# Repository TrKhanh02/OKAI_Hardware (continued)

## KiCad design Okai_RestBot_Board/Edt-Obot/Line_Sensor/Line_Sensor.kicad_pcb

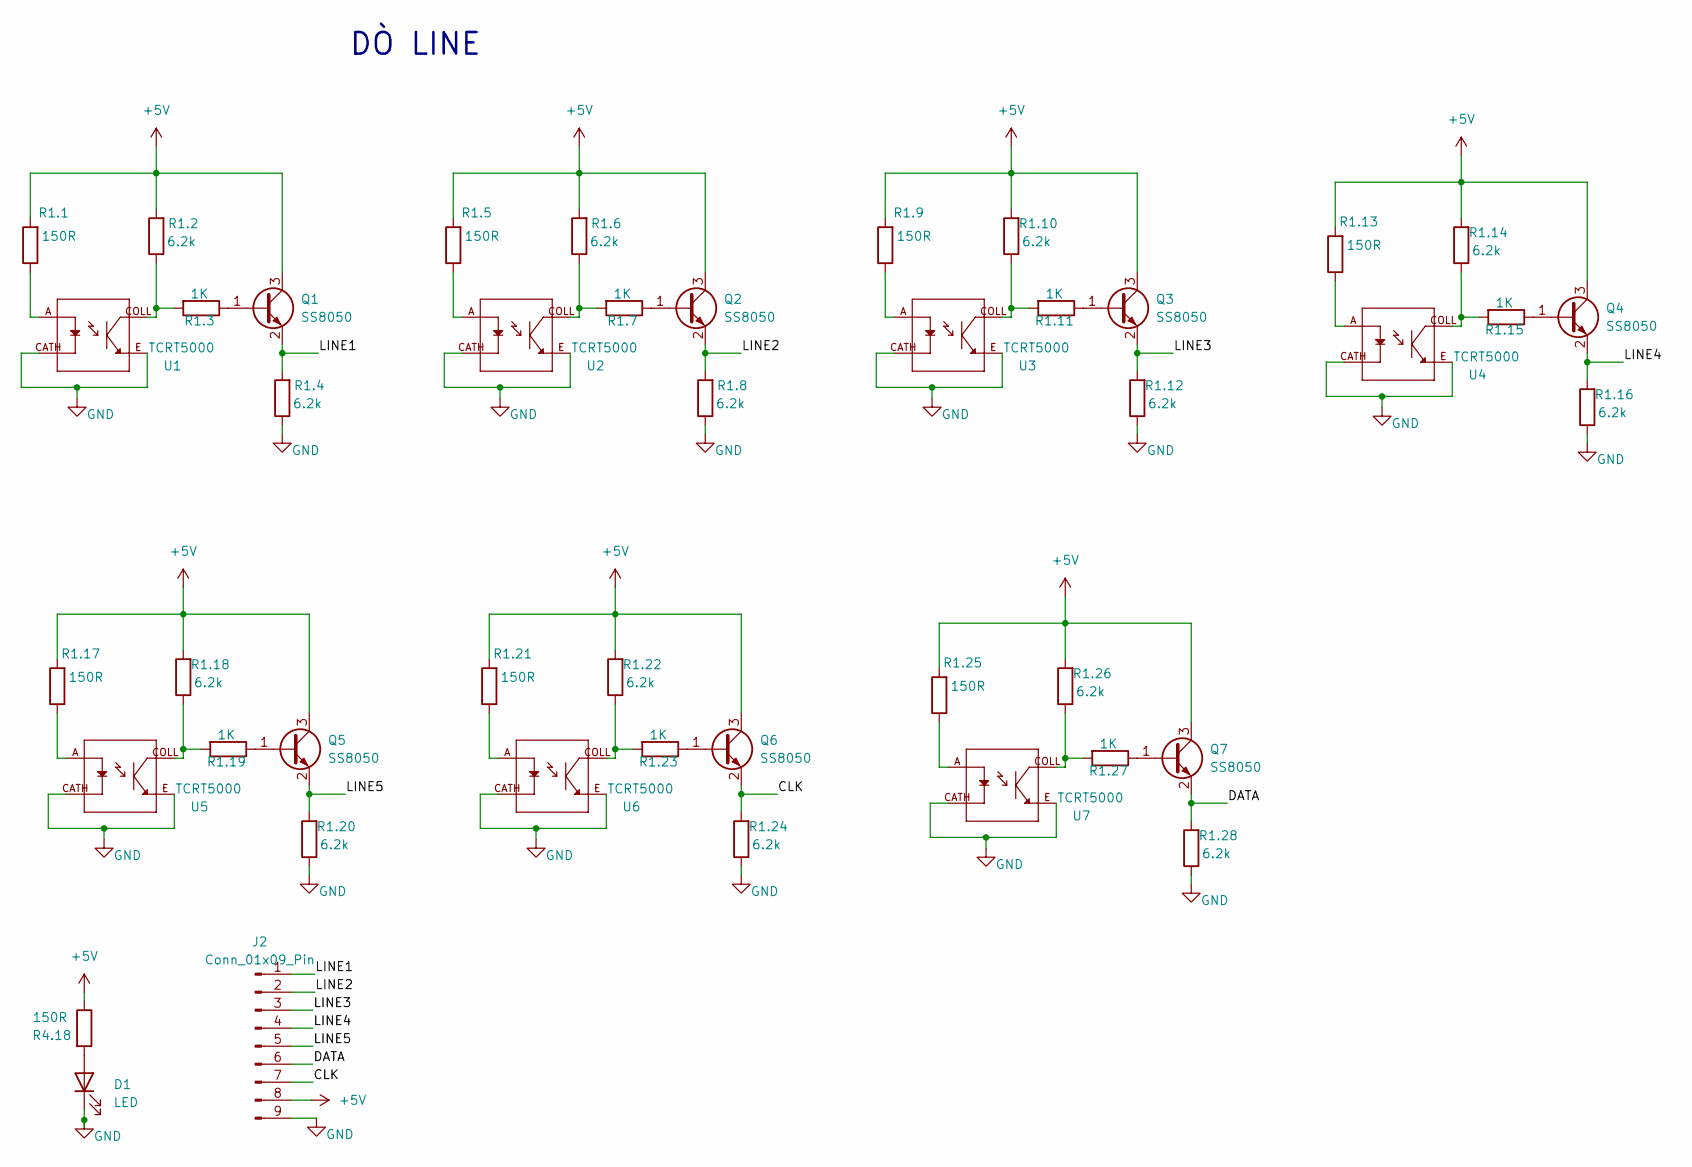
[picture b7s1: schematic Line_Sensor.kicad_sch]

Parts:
D1: LED; LED_0805_2012Metric
J2: Conn_01x09_Pin; PinHeader_1x09_P2.54mm_Vertical
Q1, Q2, Q3, Q4, Q5, Q6, Q7: SS8050; SOT-23
R1.1, R1.5, R1.9, R1.13, R1.17, R1.21, R1.25, R4.18: 150R; R_0805_2012Metric
R1.2, R1.4, R1.6, R1.8, R1.10, R1.12, R1.14, R1.16, R1.18, R1.20, R1.22, R1.24, R1.26, R1.28: 6.2k; R_0805_2012Metric
R1.3, R1.7, R1.11, R1.15, R1.19, R1.23, R1.27: 1K; R_0805_2012Metric
U1, U2, U3, U4, U5, U6, U7: TCRT5000; OPTO_TCRT5000; PARTREV 1.7

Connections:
+5V: J2.8, Q1.3 (C), Q2.3 (C), Q3.3 (C), Q4.3 (C), Q5.3 (C), Q6.3 (C), Q7.3 (C), R1.1.2, R1.2.2, R1.5.2, R1.6.2, R1.9.2, R1.10.2, R1.13.2, R1.14.2, R1.17.2, R1.18.2, R1.21.2, R1.22.2, R1.25.2, R1.26.2, R4.18.1
/CLK: J2.7, Q6.2 (E), R1.24.2
/DATA: J2.6, Q7.2 (E), R1.28.2
/LINE1: J2.1, Q1.2 (E), R1.4.2
/LINE2: J2.2, Q2.2 (E), R1.8.2
/LINE3: J2.3, Q3.2 (E), R1.12.2
/LINE4: J2.4, Q4.2 (E), R1.16.2
/LINE5: J2.5, Q5.2 (E), R1.20.2
GND: D1.1 (K), J2.9, R1.4.1, R1.8.1, R1.12.1, R1.16.1, R1.20.1, R1.24.1, R1.28.1, U1.CATH, U1.E, U2.CATH, U2.E, U3.CATH, U3.E, U4.CATH, U4.E, U5.CATH, U5.E, U6.CATH, U6.E, U7.CATH, U7.E
unnamed: D1.2 (A), R4.18.2
unnamed: Q1.1 (B), R1.3.1
unnamed: Q2.1 (B), R1.7.1
unnamed: Q3.1 (B), R1.11.1
unnamed: Q4.1 (B), R1.15.1
unnamed: Q5.1 (B), R1.19.1
unnamed: Q6.1 (B), R1.23.1
unnamed: Q7.1 (B), R1.27.1
unnamed: R1.1.1, U1.A
unnamed: R1.2.1, R1.3.2, U1.COLL
unnamed: R1.5.1, U2.A
unnamed: R1.6.1, R1.7.2, U2.COLL
unnamed: R1.9.1, U3.A
unnamed: R1.10.1, R1.11.2, U3.COLL
unnamed: R1.13.1, U4.A
unnamed: R1.14.1, R1.15.2, U4.COLL
unnamed: R1.17.1, U5.A
unnamed: R1.18.1, R1.19.2, U5.COLL
unnamed: R1.21.1, U6.A
unnamed: R1.22.1, R1.23.2, U6.COLL
unnamed: R1.25.1, U7.A
unnamed: R1.26.1, R1.27.2, U7.COLL

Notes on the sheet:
DÒ LINE

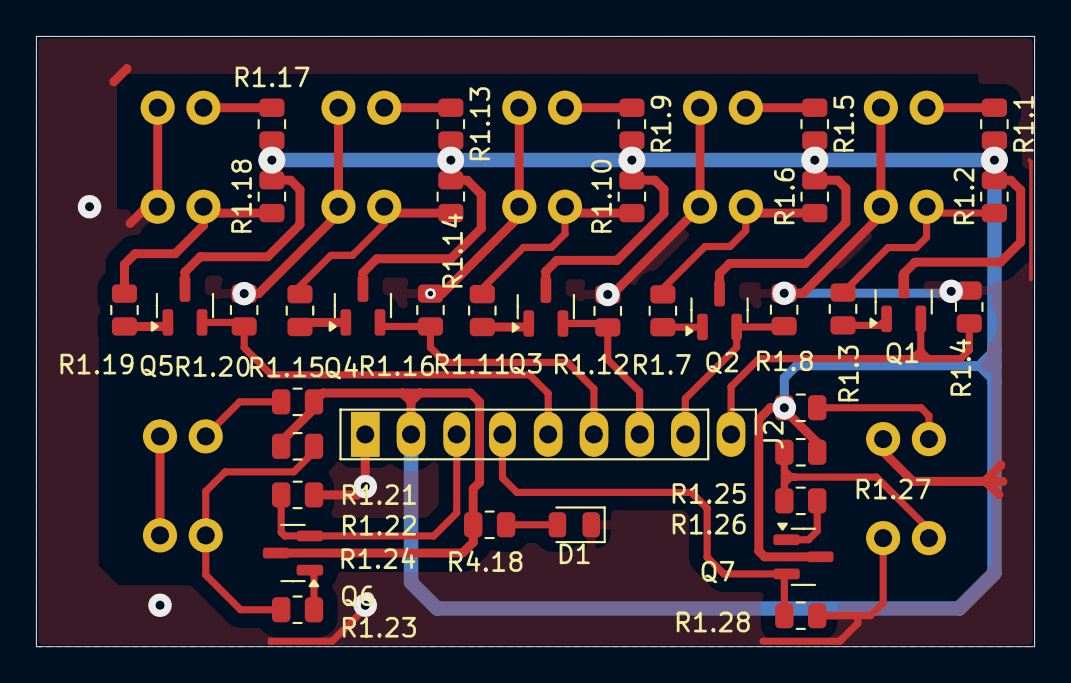
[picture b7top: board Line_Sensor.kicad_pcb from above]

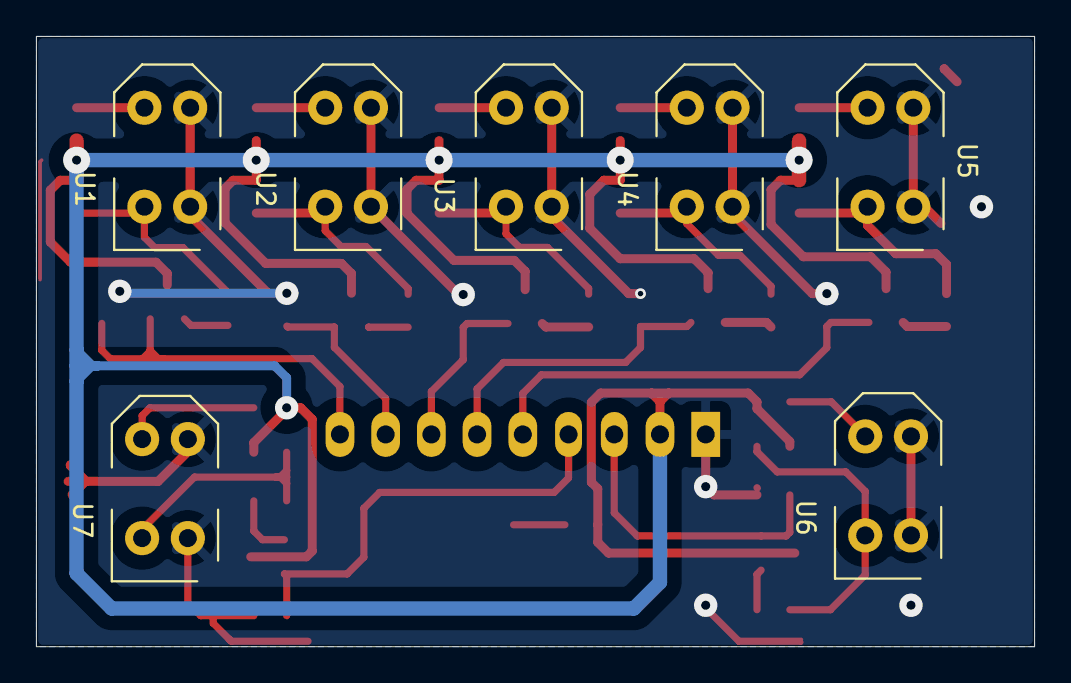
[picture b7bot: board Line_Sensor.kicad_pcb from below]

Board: 2 copper layers, 55.4 x 33.9 mm, 45 parts (7 on the bottom side), 31 nets.

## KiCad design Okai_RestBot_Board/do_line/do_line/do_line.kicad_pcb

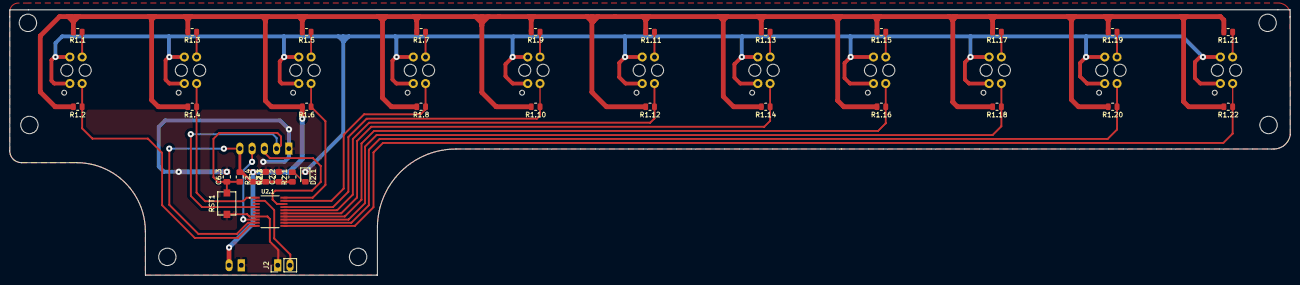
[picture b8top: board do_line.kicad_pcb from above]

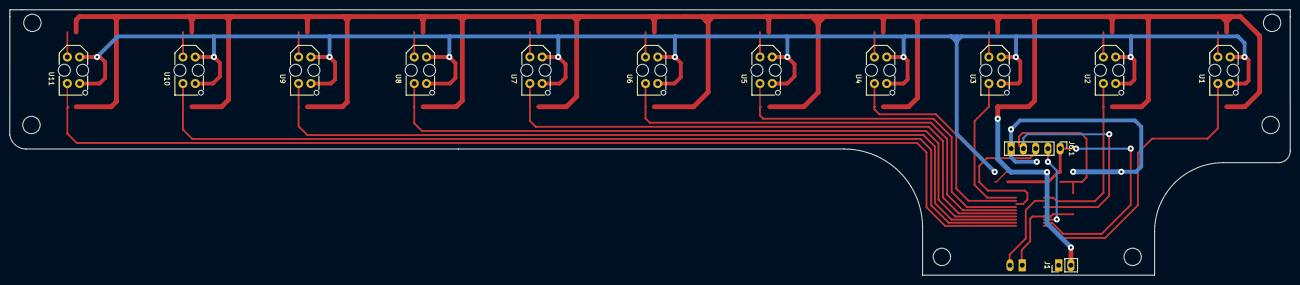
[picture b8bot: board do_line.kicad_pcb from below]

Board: 2 copper layers, 265.5 x 55.0 mm, 45 parts (13 on the bottom side), 30 nets.

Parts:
C2.1, C6.3: 104; C_0805_2012Metric_Pad1.18x1.45mm_HandSolder
C2.2: 10uF; C_0805_2012Metric_Pad1.18x1.45mm_HandSolder
D2.1: LED_Small_Filled; LED_0805_2012Metric_Pad1.15x1.40mm_HandSolder
J1, J2: Conn_01x02_Pin; PinHeader_1x02_P2.54mm_Vertical
J6.1: Conn_01x05_Pin; PinHeader_1x05_P2.54mm_Vertical
R1.1, R1.3, R1.5, R1.7, R1.9, R1.11, R1.13, R1.15, R1.17, R1.19, R1.21: 330R; R_0805_2012Metric
R1.2, R1.4, R1.6, R1.8, R1.10, R1.12, R1.14, R1.16, R1.18, R1.20, R1.22: 6.2K; R_0805_2012Metric
R2.1: 1K; R_0805_2012Metric_Pad1.20x1.40mm_HandSolder
R2.3: 0R; R_0805_2012Metric_Pad1.20x1.40mm_HandSolder
R2.4: 10k; R_0805_2012Metric_Pad1.20x1.40mm_HandSolder
RST1: TS10-63-26-BE-250-SMT-TR; SW_TS10-63-26-BE-250-SMT-TR
U1, U2, U3, U4, U5, U6, U7, U8, U9, U10, U11: TCRT5000; OPTO_TCRT5000
U2.1: N76E003AT20; SOP65P640X120-20N

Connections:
/3.3V: J1.2, R1.1.2, R1.2.2, R1.3.2, R1.4.2, R1.5.2, R1.6.2, R1.7.2, R1.8.2, R1.9.2, R1.10.2, R1.11.2, R1.12.2, R1.13.2, R1.14.2, R1.15.2, R1.16.2, R1.17.2, R1.18.2, R1.19.2, R1.20.2, R1.21.2, R1.22.2, R2.3.1
/A1: R1.1.1, U1.A
/A2: R1.3.1, U2.A
/A3: R1.5.1, U3.A
/A4: R1.7.1, U4.A
/A5: R1.9.1, U5.A
/A6: R1.11.1, U6.A
/A7: R1.13.1, U7.A
/A8: R1.15.1, U8.A
/A9: R1.17.1, U9.A
/A10: R1.19.1, U10.A
/A11: R1.21.1, U11.A
/AIN_LINE1: R1.2.1, U1.COLL, U2.1.10 (P1.5/PWM5/IC7/~SS)
/AIN_LINE2: R1.4.1, U2.COLL, U2.1.1 (P0.5/PWM2/IC6/T0/AIN4)
/AIN_LINE3: R1.6.1, U2.1.20 (P0.4/AIN5/STADC/PWM3/IC3), U3.COLL
/AIN_LINE4: R1.8.1, U2.1.19 (P0.3/PWM5/IC5/AIN6), U4.COLL
/AIN_LINE5: R1.10.1, U2.1.17 (P0.1/PWM4/IC4/MISO), U5.COLL
/AIN_LINE6: R1.12.1, U2.1.16 (P0.0/PWM3/IC3/MOSI/T1), U6.COLL
/AIN_LINE7: R1.14.1, U2.1.15 (P1.0/PWM2/IC2/SPCLK), U7.COLL
/AIN_LINE8: R1.16.1, U2.1.14 (P1.1/PWM1/IC1/AIN7/CLO), U8.COLL
/AIN_LINE9: R1.18.1, U2.1.13 (P1.2/PWM0/IC0), U9.COLL
/AIN_LINE10: R1.20.1, U2.1.12 (P1.3/SCL/[STADC]), U10.COLL
/AIN_LINE11: R1.22.1, U2.1.11 (P1.4/SDA/FB/PWM1), U11.COLL
/P0.2: J6.1.3, U2.1.18 (P0.2/ICPCK/OCDCK/RXD_1/[SCL])
/P1.6: J6.1.2, U2.1.8 (P1.6/[SDA]/TXD_1/ICPDA/OCDDA)
/P2.0: C6.3.1, J6.1.4, R2.4.2, RST1.2, U2.1.4 (P2.0/~RST)
/TXD_NE: J2.2, U2.1.2 (P0.6/TXD/AIN3)
/VDD: C2.1.1, C2.2.1, J6.1.1, R2.1.1, R2.3.2, R2.4.1, U2.1.9 (VDD)
GND: C2.1.2, C2.2.2, C6.3.2, D2.1.1 (K), J1.1, J2.1, J6.1.5, RST1.1, U1.CATH, U1.E, U2.CATH, U2.E, U2.1.7 (GND), U3.CATH, U3.E, U4.CATH, U4.E, U5.CATH, U5.E, U6.CATH, U6.E, U7.CATH, U7.E, U8.CATH, U8.E, U9.CATH, U9.E, U10.CATH, U10.E, U11.CATH, U11.E
unnamed: D2.1.2 (A), R2.1.2

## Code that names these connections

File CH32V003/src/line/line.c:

#include "line.h"

/**
 * @brief Khởi tạo GPIO cho 5 mắt Line
 * Line1: PD1, Line2: PC2, Line3: PC3, Line4: PA2, Line5: PA1
 */
void Line_Init(void) {
    GPIO_InitTypeDef GPIO_InitStructure = {0};

    // Bật Clock cho các Port A, C, D
    RCC_APB2PeriphClockCmd(RCC_APB2Periph_GPIOA | RCC_APB2Periph_GPIOC | RCC_APB2Periph_GPIOD, ENABLE);

    // Cấu hình PD1 (Line 1) - Cẩn thận vì trùng chân SWIO
    GPIO_InitStructure.GPIO_Pin = GPIO_Pin_1;
    GPIO_InitStructure.GPIO_Mode = GPIO_Mode_IPU; // Input Pull-up
    GPIO_Init(GPIOD, &GPIO_InitStructure);

    // Cấu hình PC2, PC3 (Line 2, Line 3)
    GPIO_InitStructure.GPIO_Pin = GPIO_Pin_2 | GPIO_Pin_3;
    GPIO_InitStructure.GPIO_Mode = GPIO_Mode_IPU;
    GPIO_Init(GPIOC, &GPIO_InitStructure);

    // Cấu hình PA1, PA2 (Line 4, Line 5)
    GPIO_InitStructure.GPIO_Pin = GPIO_Pin_1 | GPIO_Pin_2;
    GPIO_InitStructure.GPIO_Mode = GPIO_Mode_IPU;
    GPIO_Init(GPIOA, &GPIO_InitStructure);
}

/**
 * @brief Đọc giá trị từng mắt vào mảng
 */
void Line_Read(uint8_t *results) {
    results[0] = GPIO_ReadInputDataBit(GPIOD, GPIO_Pin_1); // L1
    results[1] = GPIO_ReadInputDataBit(GPIOC, GPIO_Pin_2); // L2
    results[2] = GPIO_ReadInputDataBit(GPIOC, GPIO_Pin_3); // L3
    results[3] = GPIO_ReadInputDataBit(GPIOA, GPIO_Pin_2); // L4
    results[4] = GPIO_ReadInputDataBit(GPIOA, GPIO_Pin_1); // L5
}

/**
 * @brief Đọc 5 mắt và gộp thành 1 byte duy nhất (Tiện cho xử lý Case-Switch)
 * Ví dụ: Nếu mắt 1 và 3 thấy vạch, trả về 0b00000101 (5)
 */
uint8_t Line_Get_Byte(void) {
    uint8_t val = 0;
    if (GPIO_ReadInputDataBit(GPIOD, GPIO_Pin_1)) val |= (1 << 0);
    if (GPIO_ReadInputDataBit(GPIOC, GPIO_Pin_2)) val |= (1 << 1);
    if (GPIO_ReadInputDataBit(GPIOC, GPIO_Pin_3)) val |= (1 << 2);
    if (GPIO_ReadInputDataBit(GPIOA, GPIO_Pin_2)) val |= (1 << 3);
    if (GPIO_ReadInputDataBit(GPIOA, GPIO_Pin_1)) val |= (1 << 4);
    return val;
}

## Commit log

2026-03-09 add hardware files
2026-03-09 convert embedded repos to normal folders
2026-03-09 Update project description from hardware to software
2026-03-09 fix folders not submodule
2026-03-09 add software files
2026-03-26 fix CH32V003 not submodule
